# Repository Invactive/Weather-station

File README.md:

# Weather-station
The PCB project of an external, autonomous weather station including a battery-powered system for monitoring atmospheric conditions using 5 weather sensors. 
The STM32 microcontroller was used to operate the sensors, while a LoRaWAN radio communication module was utilized for long-range, wireless data transmission.

## General information:

The PCB project was implemented on a FR-4 laminate with a thickness of 1.5mm and dimensions of 90x32mm, consisting of two signal layers. 

The copper tracks have a thickness of 35μm. 

The board includes a 2-pin JST-XH power connector, a programmer/debugger 8-pin connector for the microcontroller, and an SMA antenna connector. 

To obtain +5V and +3.3V voltages, two voltage converters were used (with a maximum supply voltage of +5.5V). 

The maximum current consumption calculated for the entire circuit is approximately 500mA. 

The device can be battery powered (max. input voltage 5.5V).

Data from the sensors are transmitted via I2C, SPI and Analog.

Project includes: schematics, PCB, BOM, datasheets, 3D view, Gerber and drill files.

## Modules:
- STM32 MCU
- 5 weather conditions sensors
- LoRaWAN module for wireless communication
- Battery voltage measurement unit 
- Power supply unit (includes boost converters TPS61023DRLR)

## Main Components:
- MCU - STM32F301C8T6TR
- LoraWAN - RFM95W-868S2R
- Metal Oxide Gas Sensor - MICS-6814
- Air Pressure Sensor - KP254
- Humidity Sensor - HIH6020-021-001
- Temperature Sensor - TMP36GT9Z
- Ambient Light Sensor - BH1750FVI-TR
- Boost Converter - TPS61023DRLR

## Schematics:

## PCB:

## 3D Views:

---
Project designed in KiCAD 6.0.

Author: Jakub Grzesiak

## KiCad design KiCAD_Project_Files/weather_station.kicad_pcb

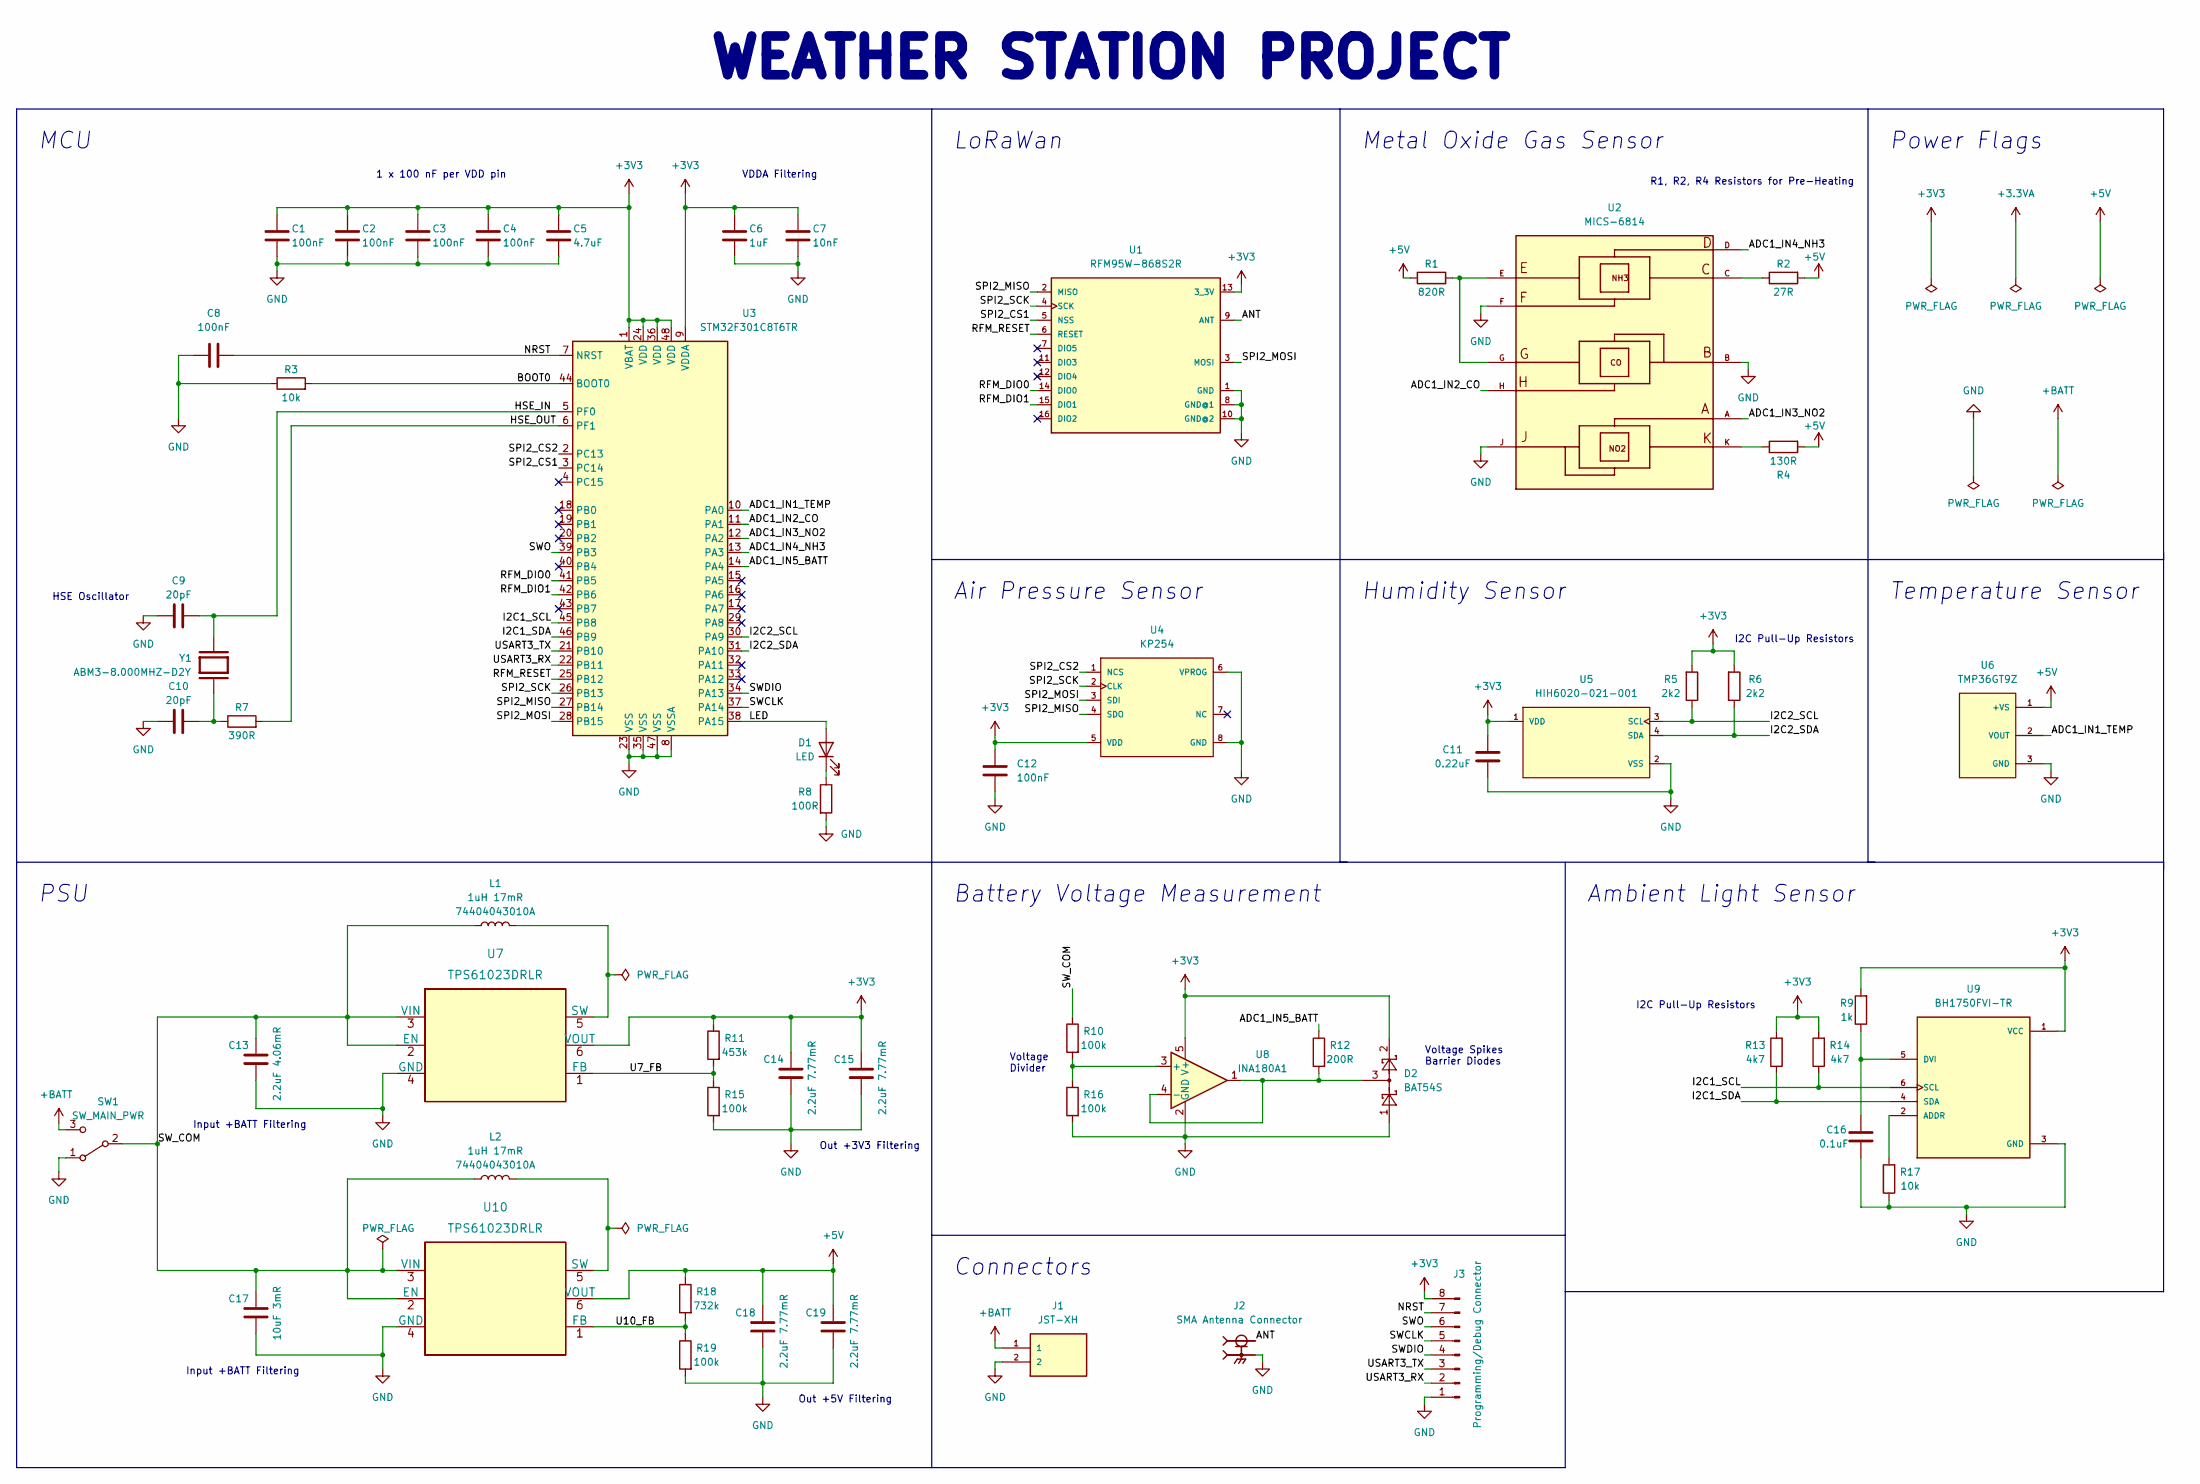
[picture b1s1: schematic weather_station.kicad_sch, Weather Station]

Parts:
C1, C2, C3, C4, C8, C12: 100nF; C_0805_2012Metric
C5: 4.7uF; C_0805_2012Metric
C6: 1uF; C_0805_2012Metric
C7: 10nF; C_0805_2012Metric
C9, C10: 20pF; C_0805_2012Metric
C11: 0.22uF; C_0805_2012Metric
C13: 2.2uF 4.06mR; C_0805_2012Metric
C14, C15: 2.2uF 7.77mR; C_0805_2012Metric; Part Num GRM21BR71E225KA73L
C16: 0.1uF; C_0805_2012Metric
C17: 10uF 3mR; C_0805_2012Metric
C18, C19: 2.2uF 7.77mR; C_0805_2012Metric
D1: LED; LED_0805_2012Metric
D2: BAT54S; SOT-23
J1: JST-XH; JST_XH_B2B-XH-A_1x02_P2.50mm_Vertical
J2: SMA Antenna Connector; MOLEX_73251-1350; PARTREV C4
J3: Programming/Debug Connector; PinHeader_1x08_P1.27mm_Vertical
L1, L2: 1uH 17mR; 74404043010A; Part Num 74404043010A
R1: 820R; R_0805_2012Metric
R2: 27R; R_0805_2012Metric
R3, R17: 10k; R_0805_2012Metric
R4: 130R; R_0805_2012Metric
R5, R6: 2k2; R_0805_2012Metric
R7: 390R; R_0805_2012Metric
R8: 100R; R_0805_2012Metric
R9: 1k; R_0805_2012Metric
R10, R15, R16, R19: 100k; R_0805_2012Metric
R11: 453k; R_0805_2012Metric
R12: 200R; R_0805_2012Metric
R13, R14: 4k7; R_0805_2012Metric
R18: 732k; R_0805_2012Metric
SW1: SW_MAIN_PWR; SW_SPDT_CK-JS102011SAQN
U1: RFM95W-868S2R; HOPERF_RFM69HW
U2: MICS-6814; SENSOR_MICS-6814
U3: STM32F301C8T6TR; LQFP-48_7x7mm_P0.5mm
U4: KP254; Infineon-KP254-Manufacturer_Recommended; Supply Voltage Range 3.3 to 5 V
U5: HIH6020-021-001; Honeywell-HIH7120-021-001-Recommended_Land_Pattern_; mouser part number 785-HIH7120-021-001; digikey description SENS HUMID/TEMP 3.3V I2C 3% 4SIP
U6: TMP36GT9Z; TO92127P521H733-3; PARTREV H
U7, U10: TPS61023DRLR
U8: INA180A1; SOT-23-5
U9: BH1750FVI-TR; XDCR_BH1750FVI-TR; PARTREV D
Y1: ABM3-8.000MHZ-D2Y; Crystal_SMD_Abracon_ABM3-2Pin_5.0x3.2mm_HandSoldering; PARTREV 4/25/2022

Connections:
+3V3: C1.2, C2.2, C3.2, C4.2, C5.2, C6.2, C7.2, C11.2, C12.1, C14.1, C15.1, D2.2, J3.8, R5.2, R6.2, R9.2, R11.1, R13.2, R14.2, U1.13 (3_3V), U3.1 (VBAT), U3.9 (VDDA), U3.24 (VDD), U3.36 (VDD), U3.48 (VDD), U4.5 (VDD), U5.1 (VDD), U7.6 (VOUT), U8.5 (V+), U9.1 (VCC)
+5V: C18.1, C19.1, R1.2, R2.2, R4.2, R18.1, U6.1 (+VS), U10.6 (VOUT)
+BATT: J1.1, SW1.3 (C)
/ADC1_IN1_TEMP: U3.10 (PA0), U6.2 (VOUT)
/ADC1_IN2_CO: U2.H, U3.11 (PA1)
/ADC1_IN3_NO2: U2.A, U3.12 (PA2)
/ADC1_IN4_NH3: U2.D, U3.13 (PA3)
/ADC1_IN5_BATT: R12.1, U3.14 (PA4)
/ANT: J2.1, U1.9 (ANT)
/BOOT0: R3.2, U3.44 (BOOT0)
/HSE_IN: C9.2, U3.5 (PF0), Y1.2
/HSE_OUT: R7.2, U3.6 (PF1)
/I2C1_SCL: R14.1, U3.45 (PB8), U9.6 (SCL)
/I2C1_SDA: R13.1, U3.46 (PB9), U9.4 (SDA)
/I2C2_SCL: R5.1, U3.30 (PA9), U5.3 (SCL)
/I2C2_SDA: R6.1, U3.31 (PA10), U5.4 (SDA)
/LED: D1.2 (A), U3.38 (PA15)
/NRST: C8.2, J3.7, U3.7 (NRST)
/RFM_DIO0: U1.14 (DIO0), U3.41 (PB5)
/RFM_DIO1: U1.15 (DIO1), U3.42 (PB6)
/RFM_RESET: U1.6 (RESET), U3.25 (PB12)
/SPI2_CS1: U1.5 (NSS), U3.3 (PC14)
/SPI2_CS2: U3.2 (PC13), U4.1 (NCS)
/SPI2_MISO: U1.2 (MISO), U3.27 (PB14), U4.4 (SDO)
/SPI2_MOSI: U1.3 (MOSI), U3.28 (PB15), U4.3 (SDI)
/SPI2_SCK: U1.4 (SCK), U3.26 (PB13), U4.2 (CLK)
/SWCLK: J3.5, U3.37 (PA14)
/SWDIO: J3.4, U3.34 (PA13)
/SWO: J3.6, U3.39 (PB3)
/SW_COM: C13.1, C17.1, L1.1, L2.1, R10.1, SW1.2 (B), U7.2 (EN), U7.3 (VIN), U10.2 (EN), U10.3 (VIN)
/U7_FB: R11.2, R15.1, U7.1 (FB)
/U10_FB: R18.2, R19.1, U10.1 (FB)
/USART3_RX: J3.2, U3.22 (PB11)
/USART3_TX: J3.3, U3.21 (PB10)
GND: C1.1, C2.1, C3.1, C4.1, C5.1, C6.1, C7.1, C8.1, C9.1, C10.1, C11.1, C12.2, C13.2, C14.2, C15.2, C16.2, C17.2, C18.2, C19.2, D2.1, J1.2, J2.S1, J2.S2, J2.S3, J2.S4, J3.1, R3.1, R8.2, R15.2, R16.2, R17.1, R19.2, SW1.1 (A), U1.1 (GND), U1.8 (GND@1), U1.10 (GND@2), U2.B, U2.F, U2.J, U3.8 (VSSA), U3.23 (VSS), U3.35 (VSS), U3.47 (VSS), U4.6 (VPROG), U4.8 (GND), U5.2 (VSS), U6.3 (GND), U7.4 (GND), U8.2 (GND), U9.3 (GND), U10.4 (GND)
unnamed: C10.2, R7.1, Y1.1
unnamed: C16.1, R9.1, U9.5 (DVI)
unnamed: D1.1 (K), R8.1
unnamed: D2.3, R12.2, U8.1, U8.4 (-)
unnamed: L1.2, U7.5 (SW)
unnamed: L2.2, U10.5 (SW)
unnamed: R1.1, U2.E, U2.G
unnamed: R2.1, U2.C
unnamed: R4.1, U2.K
unnamed: R10.2, R16.1, U8.3 (+)
unnamed: R17.2, U9.2 (ADDR)

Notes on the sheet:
Humidity Sensor
HSE Oscillator
Out +5V Filtering
Temperature Sensor
Connectors
R1, R2, R4 Resistors for Pre-Heating
Input +BATT Filtering
LoRaWan
Voltage Divider
PSU
I2C Pull-Up Resistors
Ambient Light Sensor
Metal Oxide Gas Sensor
Voltage Spikes Barrier Diodes
Out +3V3 Filtering
Power Flags
MCU
1 x 100 nF per VDD pin
VDDA Filtering
WEATHER STATION PROJECT
Air Pressure Sensor
Battery Voltage Measurement

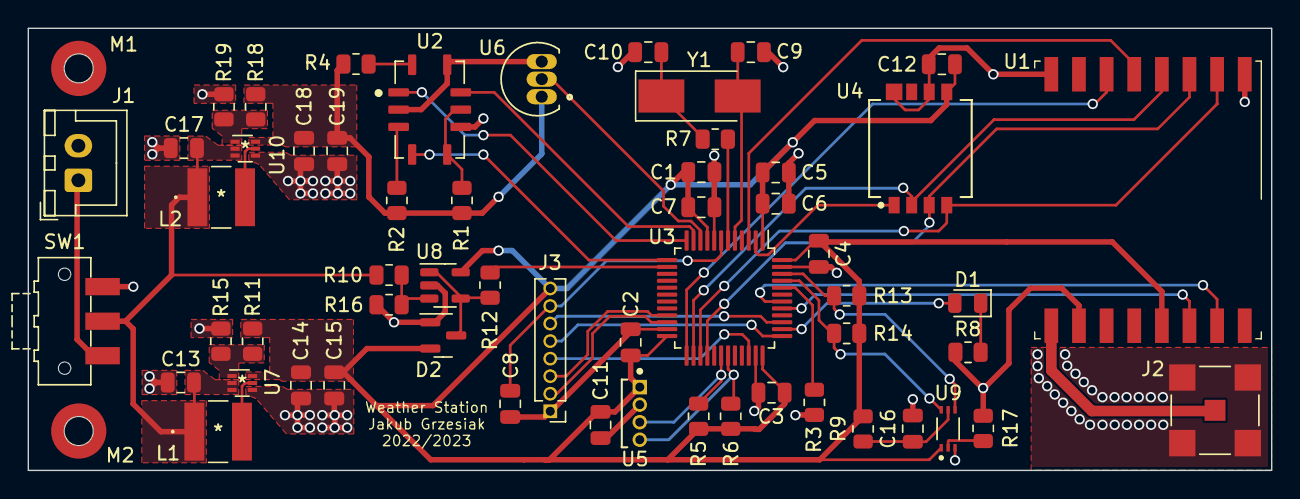
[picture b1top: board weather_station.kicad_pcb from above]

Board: 2 copper layers, 90.0 x 32.0 mm, 59 parts (0 on the bottom side), 46 nets.

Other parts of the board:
M1, M2: Mounting_Wuerth_WA-SMSI-M1.6_H2.5mm_9774025633

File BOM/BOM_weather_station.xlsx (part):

Project: | Weather Station
Author: | Jakub Grzesiak
Source: | /home/jakub/Weather station/KiCAD_Project_Files/weather_station.kicad_sch
Date: | 44928.0027777778
Tool: | Eeschema (6.0.7)
Generator: | /usr/share/kicad/plugins/bom_csv_grouped_by_value_with_fp.py
Number of components per 1 PCB: | 58
No. | Ref | Quantity | Value | Name | Footprint | Description | Vendor | Unit cost (1 item) | Price (1 PCB) | Unit cost (10 items) | Price (10 PCB) | Unit cost (100 items) | Price (100 PCB) | Link
1 | C1, C2, C3, C4, C8, C12 | 6 | 100nF | C | Capacitor_SMD:C_0805_2012Metric | Unpolarized capacitor | Mouser.pl | 0.48 zł | 2.89 zł | 0.11 zł | 6.66 zł | 0.05 zł | 31.80 zł | https://www.mouser.pl/ProductDetail/Samsung-Electro-Mechanic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
2 | C5 | 1 | 4.7uF | C | Capacitor_SMD:C_0805_2012Metric | Unpolarized capacitor | Mouser.pl | 0.48 zł | 0.48 zł | 0.18 zł | 1.83 zł | 0.15 zł | 14.90 zł | https://www.mouser.pl/ProductDetail/Samsung-Electro-Mechanic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
3 | C6 | 1 | 1uF | C | Capacitor_SMD:C_0805_2012Metric | Unpolarized capacitor | Mouser.pl | 0.48 zł | 0.48 zł | 0.18 zł | 1.83 zł | 0.15 zł | 14.90 zł | https://www.mouser.pl/ProductDetail/Samsung-Electro-Mechanic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
4 | C7 | 1 | 10nF | C | Capacitor_SMD:C_0805_2012Metric | Unpolarized capacitor | Mouser.pl | 0.48 zł | 0.48 zł | 0.12 zł | 1.15 zł | 0.10 zł | 9.60 zł | https://www.mouser.pl/ProductDetail/Samsung-Electro-Mechanic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
5 | C9, C10 | 2 | 20pF | C | Capacitor_SMD:C_0805_2012Metric | Unpolarized capacitor | Mouser.pl | 0.56 zł | 1.11 zł | 0.26 zł | 5.20 zł | 0.20 zł | 40.40 zł | https://www.mouser.pl/ProductDetail/YAGEO/CC0805JRNPO9BN200?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
6 | C11 | 1 | 0.22uF | C | Capacitor_SMD:C_0805_2012Metric | Unpolarized capacitor | Mouser.pl | 0.72 zł | 0.72 zł | 0.34 zł | 3.37 zł | 0.25 zł | 24.50 zł | https://www.mouser.pl/ProductDetail/KYOCERA-AVX/08053C224K4T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
7 | C13 | 1 | 2.2uF 4.06mR | C | Capacitor_SMD:C_0805_2012Metric | Unpolarized capacitor | Mouser.pl | 0.91 zł | 0.91 zł | 0.39 zł | 3.90 zł | 0.31 zł | 30.80 zł | https://www.mouser.pl/ProductDetail/TDK/C2012X5R1A225K085AA?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
8 | C14, C15, C18, C19 | 4 | 2.2uF 7.77mR | C | Capacitor_SMD:C_0805_2012Metric | Unpolarized capacitor | TME.eu | 1.18 zł | 4.72 zł | 1.18 zł | 47.16 zł | 0.78 zł | 310.00 zł | https://www.tme.eu/pl/en/details/grm21br71e225ka73l/mlcc-smd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
9 | C16 | 1 | 0.1uF | C | Capacitor_SMD:C_0805_2012Metric | Unpolarized capacitor | Digikey.pl | 0.45 zł | 0.45 zł | 0.20 zł | 1.99 zł | 0.11 zł | 10.90 zł | https://www.digikey.pl/en/products/detail/CL21B104KBCNNNC/12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
10 | C17 | 1 | 10uF 3mR | C | Capacitor_SMD:C_0805_2012Metric | Unpolarized capacitor | Digikey.pl | 0.63 zł | 0.63 zł | 0.47 zł | 4.67 zł | 0.22 zł | 21.90 zł | https://www.digikey.pl/en/products/detail/C0805C106K8PAC7800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
11 | D1 | 1 | LED | LED | LED_SMD:LED_0805_2012Metric | Light emitting diode | Digikey.pl | 0.86 zł | 0.86 zł | 0.86 zł | 8.60 zł | 0.68 zł | 68.40 zł | https://www.digikey.pl/en/products/detail/150080GS75000/732-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
12 | D2 | 1 | BAT54S | BAT54S | Package_TO_SOT_SMD:SOT-23 | Schottky barrier diode | Mouser.pl | 0.87 zł | 0.87 zł | 0.82 zł | 8.23 zł | 0.45 zł | 45.20 zł | https://www.mouser.pl/ProductDetail/onsemi/BAT54SLT1G?qs=vLk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
13 | J1 | 1 | JST-XH | B2B-XH-A(LF)(SN) | Connector_JST:JST_XH_B2B-XH-A_1x02_P2.50mm_Vertical | JST-XH header connector 2-pin | Farnell.com | 0.42 zł | 0.42 zł | 0.42 zł | 4.20 zł | 0.42 zł | 42.00 zł | https://pl.farnell.com/jst-japan-solderless-terminals/b2b-xh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
14 | J2 | 1 | SMA Antenna Connector | 73251-1350 | MOLEX_SMA_73251-1350:MOLEX_73251-1350 | SMA header antenna connector | Digikey.pl | 19.12 zł | 19.12 zł | 16.82 zł | 168.20 zł | 13.38 zł | 1338.00 zł | https://www.digikey.pl/en/products/detail/0732511350/WM9357-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
15 | J3 | 1 | Debug Connector | Conn_01x08_Male | Connector_PinHeader_1.27mm:PinHeader_1x08_P1.27mm_Vertical | Generic connector, single row, 01x08, script generated (kicad-library-utils/sch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 | TME.eu | 0.93 zł | 0.93 zł | 0.93 zł | 9.26 zł | 0.58 zł | 58.10 zł | https://www.tme.eu/en/details/zl319-8p/pin-headers/connfly/d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
16 | L1, L2 | 2 | 1uH 17mR | L | 74404043010A:74404043010A | Inductor 74404043010A | Mouser.pl | 3.03 zł | 6.06 zł | 3.03 zł | 60.60 zł | 1.93 zł | 386.00 zł | https://www.mouser.pl/ProductDetail/Wurth-Elektronik/7440404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
17 | R1 | 1 | 820R | R | Resistor_SMD:R_0805_2012Metric | Resistor | Digikey.pl | 0.45 zł | 0.45 zł | 0.21 zł | 2.08 zł | 0.09 zł | 8.50 zł | https://www.digikey.pl/en/products/detail/CRGCQ0805F820R/A12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
18 | R2 | 1 | 27R | R | Resistor_SMD:R_0805_2012Metric | Resistor | Digikey.pl | 0.45 zł | 0.45 zł | 0.21 zł | 2.08 zł | 0.09 zł | 8.50 zł | https://www.digikey.pl/en/products/detail/CRG0805F27R/A12635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
19 | R3, R17 | 2 | 10k | R | Resistor_SMD:R_0805_2012Metric | Resistor | Digikey.pl | 0.45 zł | 0.90 zł | 0.16 zł | 3.18 zł | 0.07 zł | 13.00 zł | https://www.digikey.pl/en/products/detail/CRGCQ0805J10K/A130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
20 | R4 | 1 | 130R | R | Resistor_SMD:R_0805_2012Metric | Resistor | Digikey.pl | 0.45 zł | 0.45 zł | 0.30 zł | 3.04 zł | 0.12 zł | 12.30 zł | https://www.digikey.pl/en/products/detail/CRCW0805130RFKEA/5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
21 | R5, R6 | 2 | 2k2 | R | Resistor_SMD:R_0805_2012Metric | Resistor | Digikey.pl | 0.45 zł | 0.90 zł | 0.17 zł | 3.36 zł | 0.07 zł | 13.60 zł | https://www.digikey.pl/en/products/detail/CRGCQ0805J2K2/A130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
22 | R7 | 1 | 390R | R | Resistor_SMD:R_0805_2012Metric | Resistor | Digikey.pl | 0.45 zł | 0.45 zł | 0.40 zł | 3.99 zł | 0.15 zł | 15.40 zł | https://www.digikey.pl/en/products/detail/ERJ-6ENF3900V/P390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
23 | R8 | 1 | 100R | R | Resistor_SMD:R_0805_2012Metric | Resistor | Digikey.pl | 0.50 zł | 0.50 zł | 0.44 zł | 4.39 zł | 0.17 zł | 16.90 zł | https://www.digikey.pl/en/products/detail/CRGH0805F100R/A126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
24 | R9 | 1 | 1k | R | Resistor_SMD:R_0805_2012Metric | Resistor | Digikey.pl | 0.45 zł | 0.45 zł | 0.16 zł | 1.63 zł | 0.07 zł | 6.70 zł | https://www.digikey.pl/en/products/detail/RC0805FR-101KL/13-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
25 | R10, R15, R16, R19 | 4 | 100k | R | Resistor_SMD:R_0805_2012Metric | Resistor | Mouser.pl | 0.48 zł | 1.92 zł | 0.25 zł | 10.00 zł | 0.11 zł | 44.40 zł | https://www.mouser.pl/ProductDetail/Bourns/CR0805AFX-1003ELF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
26 | R11 | 1 | 453k | R | Resistor_SMD:R_0805_2012Metric | Resistor | Mouser.pl | 0.53 zł | 0.53 zł | 0.40 zł | 4.04 zł | 0.16 zł | 15.90 zł | https://www.mouser.pl/ProductDetail/Panasonic/ERJ-6ENF4533V?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
27 | R12 | 1 | 200R | R | Resistor_SMD:R_0805_2012Metric | Resistor | Digikey.pl | 0.45 zł | 0.45 zł | 0.11 zł | 1.13 zł | 0.05 zł | 4.70 zł | https://www.digikey.pl/en/products/detail/CR0805-FX-2000ELF/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
28 | R13, R14 | 2 | 4k7 | R | Resistor_SMD:R_0805_2012Metric | Resistor | Digikey.pl | 0.45 zł | 0.90 zł | 0.21 zł | 4.16 zł | 0.09 zł | 17.00 zł | https://www.digikey.pl/en/products/detail/CRGCQ0805F4K7/A129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
29 | R18 | 1 | 732k | R | Resistor_SMD:R_0805_2012Metric | Resistor | Mouser.pl | 0.48 zł | 0.48 zł | 0.40 zł | 4.04 zł | 0.16 zł | 15.90 zł | https://www.mouser.pl/ProductDetail/Panasonic/ERJ-6ENF7323V?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
30 | SW1 | 1 | SW_MAIN_PWR | SW_SPDT | Button_Switch_SMD:SW_SPDT_CK-JS102011SAQN | Switch, single pole double throw | Digikey.pl | 2.99 zł | 2.99 zł | 2.90 zł | 29.04 zł | 2.79 zł | 279.40 zł | https://www.digikey.pl/en/products/detail/c-k/JS102011SAQN/1640095
31 | U1 | 1 | RFM95W-868S2 | RFM95W-868S2 | RF_Module:HOPERF_RFM69HW | LoraWAN module | TME.eu | 36.36 zł | 36.36 zł | 30.71 zł | 397.10 zł | 25.11 zł | 2511.00 zł | https://www.tme.eu/pl/en/details/rfm95w-868s2/rf-modules/hop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
32 | U2 | 1 | MICS-6814 | MICS-6814 | MICS-6814:SENSOR_MICS-6814 | Air Quality Sensors MOS Triple Sensor | Mouser.pl | 58.49 zł | 58.49 zł | 53.73 zł | 573.30 zł | 53.20 zł | 5320.00 zł | https://www.mouser.pl/ProductDetail/Amphenol-SGX-Sensortech/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
33 | U3 | 1 | STM32F301C8T6TR | STM32F301C8Tx | Package_QFP:LQFP-48_7x7mm_P0.5mm | ARM Cortex-M4 MCU, 64KB flash, 16KB RAM, 72MHz, 2-3.6V, 37 GPIO, LQFP-48 | Farnell.com | 18.83 zł | 18.83 zł | 16.92 zł | 169.20 zł | 13.84 zł | 1384.00 zł | https://pl.farnell.com/stmicroelectronics/stm32f301c8t6tr/mc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

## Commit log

2023-04-22 BOM, schematics, gerbers and KiCAD files
2023-04-22 Datasheets and src files
2023-04-22 Fixed schematics .pdf
2023-05-28 Updated PCB and added 3D view
2023-05-28 Fixed schematics and src files

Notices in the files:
parts and their libraries:
Copyright 2021 Accelerated Designs. All rights reserved.
